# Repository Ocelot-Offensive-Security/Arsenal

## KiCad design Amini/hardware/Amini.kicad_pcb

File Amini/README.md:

# Amini Project

The project is divided in three different sections:
* ArduinoBLE
* examples
* hardware

## ArduinoBLE
The ArduinoBLE contains the modified Bluetooth BLE library to handle the Apple AirTags advertising packages and special features regarding scanning, detection and spoofing. To use this library, just copy and paste it into the Arduino library section.

Some of the most important changes in the Arduino BLE library could be found into the advertising packages handler.

To obtain the advertising packages data at BLEDevice.cpp:
```
int BLEDevice::getAdvertisement(uint8_t value[], int length)
{
  if (_eirDataLength) {
    memcpy(value, _eirData, length);
  }

  return _eirDataLength;
}
```
To be able to advertise an AirTag package, we modified the flags assignation at local/BLELocalDevice.cpp:
```
BLELocalDevice::BLELocalDevice()
{
  //_advertisingData.setFlags(BLEFlagsGeneralDiscoverable | BLEFlagsBREDRNotSupported);
}
```

## Examples
In contains different examples to be used with supported Arduino-environment boards.
- leds: detecting AirTag presence by flashing LEDs depending on signal strength
- scan: continuous scanning to detect enabled and disabled AirTags 
- sound: detecting enabled AirTags and connected to them to generated a register, if after 10 minutes the AirTags are nearby, Amini can force to play a sound
- spoof: simulates an AirTag behavior for packaging advertising 

## Hardware
It contains the open-hardware board presented in Black Hat USA Arsenal on Aug 11th, 2022. https://www.blackhat.com/us-22/arsenal/schedule/index.html#amini-project-27224

### LEDs and Buttons pins
LEDs:
- Pin 18: D3
- Pin 19: D6
- Pin 21: D5
- Pin 22: D4

Buttons:
- Pin 7: SW3
- Pin 8: SW4

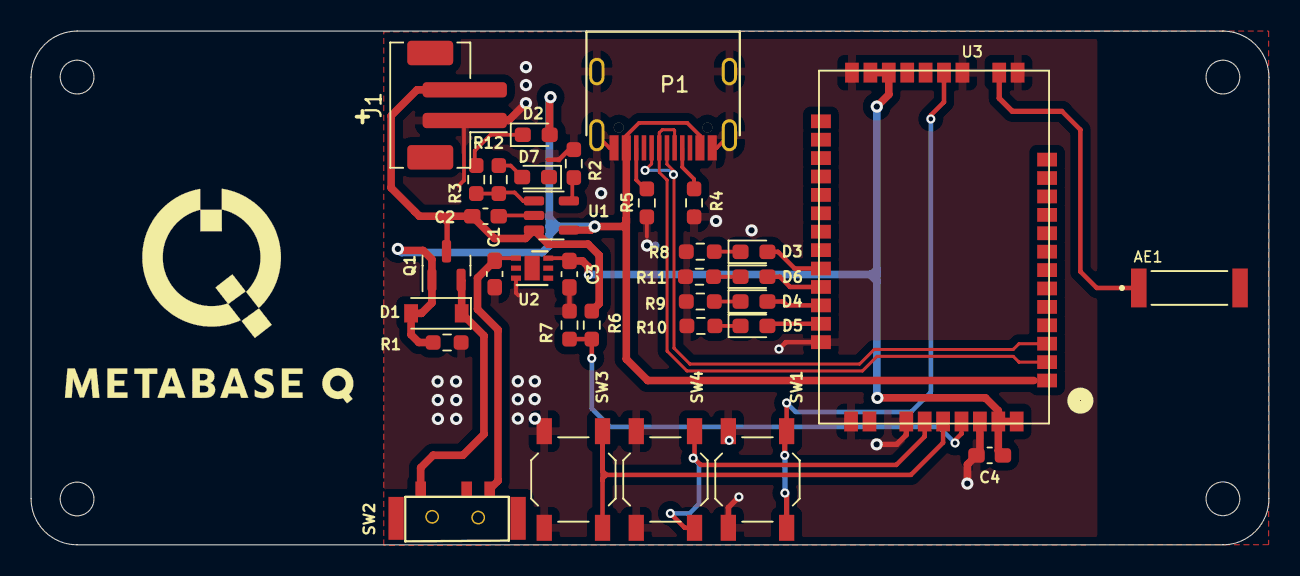
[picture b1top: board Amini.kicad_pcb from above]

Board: 2 copper layers, 80.7 x 33.5 mm, 38 parts (0 on the bottom side), 27 nets.

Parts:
AE1: Antenna; XDCR_ANT-2.45-CHP-T
C1, C2, C3: 10uF; C_0603_1608Metric_Pad1.08x0.95mm_HandSolder
C4: 0.1uF; C_0603_1608Metric_Pad1.08x0.95mm_HandSolder
D1: MBR120; D_SOD-123
D2: CHR; LED_0603_1608Metric_Pad1.05x0.95mm_HandSolder
D3: USR1; LED_0603_1608Metric_Pad1.05x0.95mm_HandSolder
D4: USR3; LED_0603_1608Metric_Pad1.05x0.95mm_HandSolder
D5: USR4; LED_0603_1608Metric_Pad1.05x0.95mm_HandSolder
D6: USR2; LED_0603_1608Metric_Pad1.05x0.95mm_HandSolder
D7: DONE; LED_0603_1608Metric_Pad1.05x0.95mm_HandSolder
H1, H2, H3, H4: MountingHole; MountingHole_2.2mm_M2
J1: Conn_Battery; JST_PH_B2B-PH-SM4-TB_1x02-1MP_P2.00mm_Vertical
P1: USB_C_Plug_USB2.0; C393939
Q1: DMG3415U-7; SOT-23
R1, R6, R7: 100K; R_0603_1608Metric_Pad0.98x0.95mm_HandSolder
R2: 2.2K; R_0603_1608Metric_Pad0.98x0.95mm_HandSolder
R3, R8, R9, R10, R11, R12: 1K; R_0603_1608Metric_Pad0.98x0.95mm_HandSolder
R4, R5: 5.1k; R_0603_1608Metric_Pad0.98x0.95mm_HandSolder
SW1: RESET; SW_SPST_TL3342
SW2: ON; Micro_interruptor_SPDT
SW3: D9; SW_SPST_TL3342
SW4: D8; SW_SPST_TL3342
U1: MCP73831-3-OT; SOT-23-5
U2: MCP1700_DFN6; DFN-6-1EP_2x2mm_P0.65mm_EP1x1.6mm
U3: RAK4630

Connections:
+3V3: C3.1, C4.1, U2.6 (VO), U3.20 (VBAT_SX), U3.21 (VBAT_IO_SX), U3.43 (VDD), U3.44 (VBAT)
+BATT: C2.1, J1.2, Q1.3 (D), R6.1, U1.3 (VBAT)
/A0: R6.2, R7.1, U3.41 (P0.04/AIN2)
/D8: SW4.2, U3.39 (P0.31/AIN7)
/D9: SW3.2, U3.40 (P0.05/AIN3)
/D10: D4.2 (A), U3.33 (P0.30/QSPI_DIO0)
/D11: D5.2 (A), U3.34 (P0.26/QSPI_CS)
/D12: D6.2 (A), U3.32 (P0.29/QSPI_DIO1)
/D13: D3.2 (A), U3.31 (P0.28/QSPI_DIO2)
/D+: P1.A6 (D+), U3.3 (D+)
/D-: P1.A7 (D-), U3.2 (D-)
/RST: SW1.2, U3.17 (RST)
GND: C1.2, C2.2, C3.2, C4.2, D7.1 (K), J1.1, P1.A1 (GND), P1.S1 (SHIELD), R1.2, R2.2, R4.1, R5.1, R7.2, R8.2, R9.2, R10.2, R11.2, SW1.1, SW3.1, SW4.1, U1.2 (VSS), U2.3 (GND), U3.14 (GND), U3.16 (GND), U3.22 (GND), U3.35 (GND), U3.36 (GND), U3.38 (GND), U3.42 (GND)
unnamed: C1.1, SW2.2 (B), U2.1 (VI)
unnamed: D1.1 (K), Q1.2 (S), SW2.1 (A)
unnamed: D2.1 (K), R3.2
unnamed: D3.1 (K), R8.1
unnamed: D4.1 (K), R9.1
unnamed: D5.1 (K), R10.1
unnamed: D6.1 (K), R11.1
unnamed: D7.2 (A), R12.2
unnamed: P1.A5 (CC), R4.2
unnamed: P1.B5 (VCONN), R5.2
unnamed: R2.1, U1.5 (PROG)
unnamed: R3.1, R12.1, U1.1 (STAT)
unnamed: AE1.1 (A), U3.15 (RF_BT)
VBUS: D1.2 (A), D2.2 (A), P1.A4 (VBUS), Q1.1 (G), R1.1, U1.4 (VDD), U3.1 (VBUS)

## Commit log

2022-11-09 Fix typo
